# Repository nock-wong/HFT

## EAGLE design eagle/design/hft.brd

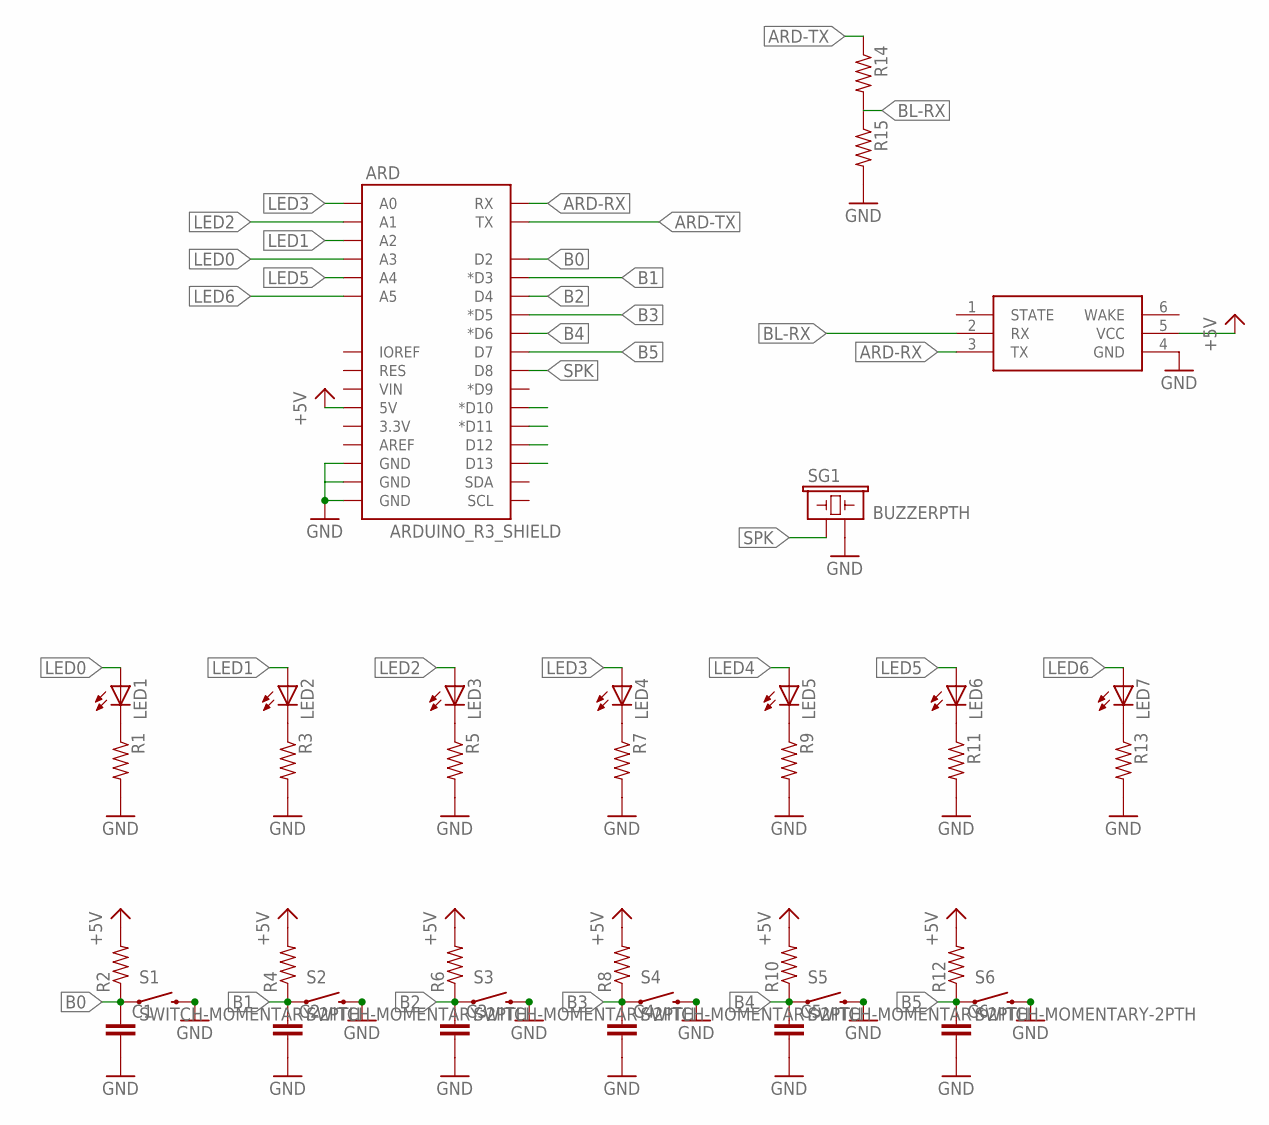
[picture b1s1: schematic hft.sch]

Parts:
ARD: ARDUINO_R3_SHIELD; UNO_R3_SHIELD
C1, C2, C3, C4, C5, C6: CAPACITOR0603-CAP; 0603-CAP
LED1, LED2, LED3, LED4, LED5, LED6, LED7: LED5MM
R1, R2, R3, R4, R5, R6, R7, R8, R9, R10, R11, R12, R13, R14, R15: RESISTOR; 0603-RES
S1, S2, S3, S4, S5, S6: SWITCH-MOMENTARY-2PTH; TACTILE-PTH
SG1: BUZZERPTH; BUZZER-12MM
U$8: HC-06; HC-06_BREAKOUT

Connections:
+5V: ARD.5V, R2.2, R4.2, R6.2, R8.2, R10.2, R12.2, U$8.5 (VCC)
ARD-RX: ARD.RX, U$8.3 (TX)
ARD-TX: ARD.TX, R14.1
B0: ARD.D2, C1.1, R2.1, S1.1
B1: ARD.D3 (*D3), C2.1, R4.1, S2.1
B2: ARD.D4, C3.1, R6.1, S3.1
B3: ARD.D5 (*D5), C4.1, R8.1, S4.1
B4: ARD.D6 (*D6), C5.1, R10.1, S5.1
B5: ARD.D7, C6.1, R12.1, S6.1
BL-RX: R14.2, R15.1, U$8.2 (RX)
GND: ARD.GND@0 (GND), ARD.GND@1 (GND), ARD.GND@2 (GND), C1.2, C2.2, C3.2, C4.2, C5.2, C6.2, R1.2, R3.2, R5.2, R7.2, R9.2, R11.2, R13.2, R15.2, S1.3 (2), S2.3 (2), S3.3 (2), S4.3 (2), S5.3 (2), S6.3 (2), SG1.- (2), U$8.4 (GND)
LED0: ARD.A3, LED1.A
LED1: ARD.A2, LED2.A
LED2: ARD.A1, LED3.A
LED3: ARD.A0, LED4.A
LED4: LED5.A
LED5: ARD.A4, LED6.A
LED6: ARD.A5, LED7.A
unnamed: LED1.K (C), R1.1
unnamed: LED2.K (C), R3.1
unnamed: LED3.K (C), R5.1
unnamed: LED4.K (C), R7.1
unnamed: LED5.K (C), R9.1
unnamed: LED6.K (C), R11.1
unnamed: LED7.K (C), R13.1
SPK: ARD.D8, SG1.+ (1)

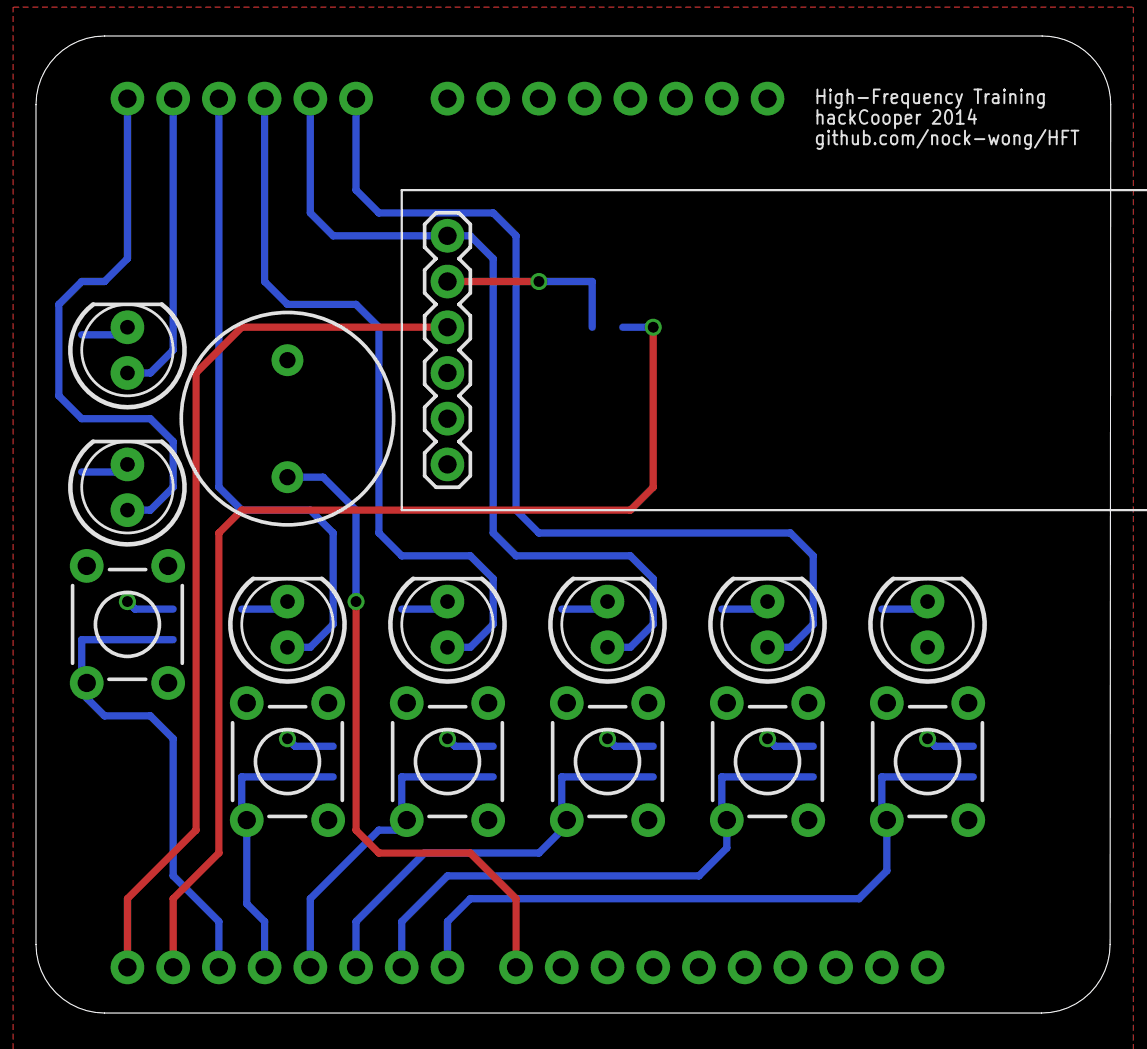
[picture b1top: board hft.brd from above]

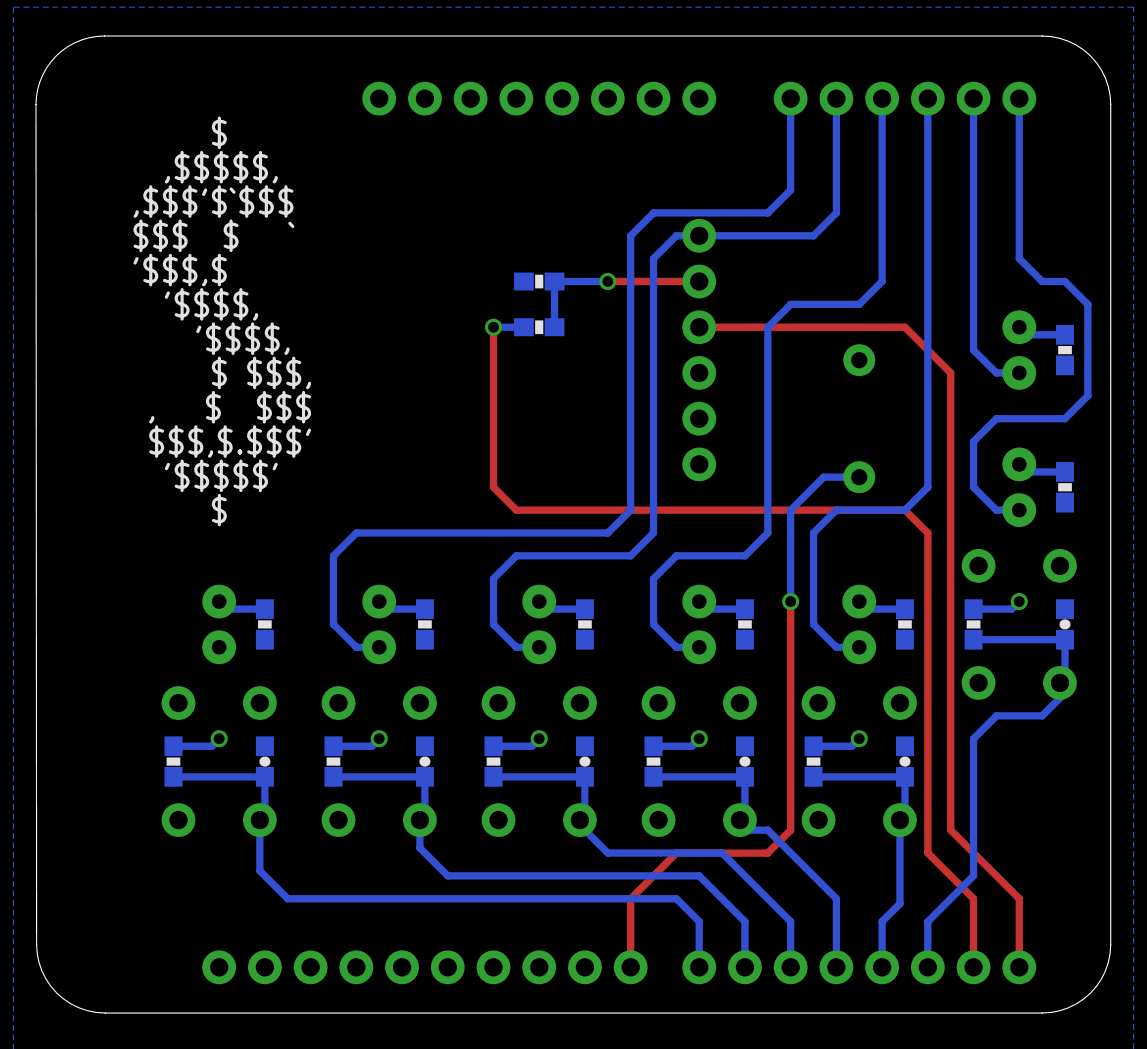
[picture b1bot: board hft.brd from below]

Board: 2 copper layers, 59.7 x 54.3 mm, 37 parts (21 on the bottom side), 25 nets.

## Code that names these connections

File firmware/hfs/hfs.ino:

#define COMMAND_BUTTON_STATES 'A'
#define COMMAND_GAME_LIGHTS 'B'
#define COMMAND_WON_OR_LOSE 'C'
#define COMMAND_END_CHAR 'X'
#define COMMAND_CONNECT 'F'
#define COMMAND_START 'D'
#define COMMAND_READY 'E'
#define COMMAND_GAME_END 'G'

#define LED0 8
#define LED1 9
#define LED2 10
#define LED3 11
#define LED4 12
#define LEDLOSE 2
#define LEDWIN 3
#define BUZZER 13
#define BUTTON0 A4
#define BUTTON1 A3
#define BUTTON2 A2
#define BUTTON3 A1
#define BUTTON4 A0

#define NOT_READY 0
#define READY 1

#define LOSE 0
#define WIN 1
#define NEUTRAL 2

#define BAUD 9600
#define LED_COUNT 5
#define BUTTON_COUNT 5
#define COMMAND_SIZE 20

const int g_leds_pins[LED_COUNT] = {LED0, LED1,LED2, LED3, LED4};
const int g_buttons_pins[BUTTON_COUNT] = {BUTTON0, BUTTON1, BUTTON2, BUTTON3, BUTTON4};

int g_command_ready = false;
int g_command_index = 0;
int g_command_in[COMMAND_SIZE];

int g_buttons_changed = false;
int g_leds_states[] = {0, 0, 0, 0, 0};
int g_buttons[] = {0, 0, 0, 0, 0};

int g_connected = false;
int g_start = false;
int g_end = false;

int g_won = NEUTRAL;

void 
setup (void) 
{
  pinMode(LED0, OUTPUT);
  pinMode(LED1, OUTPUT);
  pinMode(LED2, OUTPUT);
  pinMode(LED3, OUTPUT);
  pinMode(LED4, OUTPUT);
  pinMode(LEDWIN, OUTPUT);
  pinMode(LEDLOSE, OUTPUT);
  
  pinMode(BUTTON0, INPUT);
  pinMode(BUTTON1, INPUT);
  pinMode(BUTTON2, INPUT);
  pinMode(BUTTON3, INPUT);
  pinMode(BUTTON4, INPUT);

  pinMode(BUZZER, OUTPUT);
  Serial.begin(BAUD);
}

void
loop (void)
{ 
  // Wait for connection to game
  while(g_connected == false)
  {
    send_connect();
    read_command();
    delay(500);
  }
  // Wait for game to start
  while(g_start == false)
  {
    read_command();
  }
  // Game start
  while(g_start == true && g_end == false)
  {
    g_won = NEUTRAL;
    read_command();
    update_display();
    read_buttons();
    if (g_buttons_changed == true)
    {
      send_buttons_states();
    }
  }
  // Game end
  g_connected = false;
  g_start = false;
  g_end = false;
}

void send_connect()
{
  Serial.print(COMMAND_CONNECT);
  Serial.print(COMMAND_END_CHAR);
}

void read_command() 
{
  while (Serial.available())
  {
    int r = Serial.read();
    g_command_in[g_command_index] = r;
    g_command_index++;
    if (r == COMMAND_END_CHAR)
    {
      process_command();
    }
  }
  return;
}

void process_command()
{
  // Confirm connect
  if (g_command_in[0] == COMMAND_CONNECT)
  {
    g_connected = true;
  }
  // Start game
  if (g_command_in[0] == COMMAND_START)
  {
    g_start = true;
    start_sequence();
    send_ready();
  }
  // Sets the game lights
  if (g_command_in[0] == COMMAND_GAME_LIGHTS)
  {
    for (int i = 0; i < LED_COUNT; i++)
    {
      int state = LOW;
      switch(g_command_in[i+1])
      {
        case '0':
          state = LOW;
          break;
        case '1':
          state = HIGH;
          break;
        default:
          state = LOW;
          break;
      }
      g_leds_states[i] = state;
    }
  }
  // Sets the WIN/LOSE lights
  else if (g_command_in[0] == COMMAND_WON_OR_LOSE)
  {
    int state = LOSE;
    if (g_command_in[1] == '0')
    {
      state = LOSE;
    }
    else if (g_command_in[1] == '1')
    {
      state = WIN;
    }
    else if (g_command_in[1] == '2')
    {
      state = NEUTRAL;
    }
    g_won = state;
   }
  // Sets the end game
  else if (g_command_in[0] == COMMAND_GAME_END)
  {
    g_end = true;
    if (g_command_in[1] == '1')
    {
      digitalWrite(LEDLOSE, LOW);      
      digitalWrite(LEDWIN, HIGH);
      win();
    }
    else if (g_command_in[1] == '0')
    {
      digitalWrite(LEDLOSE, HIGH);      
      digitalWrite(LEDWIN, LOW);
      lose();
    } 
  }
  clear_command_in();
}

void start_sequence()
{
  /*
  for(int i = 0; i < LED_COUNT; i++)
  {
    digitalWrite(g_leds_pins[i], HIGH);
  }
  */
  digitalWrite(LEDLOSE, HIGH);
  playMelody("c", 1000);
  digitalWrite(LEDLOSE, LOW);
  delay(100);
  
  digitalWrite(LEDLOSE, HIGH);
  playMelody("c", 1000);
  digitalWrite(LEDLOSE, LOW);
  delay(100);
  
  digitalWrite(LEDLOSE, HIGH);
  playMelody("c", 1000);
  digitalWrite(LEDLOSE, LOW);
  delay(100);

  digitalWrite(LEDWIN, HIGH);
  playMelody("z", 1000);  
  /*
  for (int j = 0; j < 3; j++)
  {
    for(int i = 0; i < LED_COUNT; i++)
    {
      digitalWrite(g_leds_pins[i], HIGH);
    }
    delay(500);
    for(int i = 0; i < LED_COUNT; i++)
    {
      digitalWrite(g_leds_pins[i], LOW);
    }
    delay(500);
  }
  */
  return;
}

void send_ready()
{
  Serial.print(COMMAND_READY);
  Serial.print(COMMAND_END_CHAR);
  return;
}

void update_display() 
{
  for (int i = 0; i < 5; i++)
  {
    digitalWrite(g_leds_pins[i], g_leds_states[i]);
  }
  switch (g_won)
  {
    case WIN:
      digitalWrite(LEDWIN, HIGH);
      digitalWrite(LEDLOSE, LOW);
      correct();
      break;
    case LOSE:
      digitalWrite(LEDWIN, LOW);
      digitalWrite(LEDLOSE, HIGH);
      incorrect();
      break;
    case NEUTRAL:
      digitalWrite(LEDWIN, LOW);
      digitalWrite(LEDLOSE, LOW);
      break;
  }
  return;
}

void clear_command_in ()
{
  for (int i = 0; i < COMMAND_SIZE; i++)
  {
    g_command_in[i] = 0;
  }
  g_command_index = 0;
  g_command_ready = false;
  return;
}

void send_buttons_states()
{
  Serial.print(COMMAND_BUTTON_STATES);
  for (int i = 0; i < BUTTON_COUNT; i++)
  {
    Serial.print(g_buttons[i]);
  }
  Serial.print(COMMAND_END_CHAR);
}

void read_buttons (void)
{
  g_buttons_changed = false;
  int buttons_readings[BUTTON_COUNT];
  // Read buttons
  for (int i = 0; i < BUTTON_COUNT; i++)
  {
    buttons_readings[i] = !digitalRead(g_buttons_pins[i]);
  }
  // Compare current to previous
  boolean buttons_different = false;
  for (int i = 0; i < BUTTON_COUNT; i++) 
  {
    if (g_buttons[i] != buttons_readings[i])
    {
      g_buttons[i] = buttons_readings[i];
      buttons_different = true;
    }
  }
  // Check that buttons aren't all 0
  boolean buttons_all_zero = true;
  for (int i = 0; i < BUTTON_COUNT; i++) 
  {
    if (g_buttons[i] != 0)
    {
      buttons_all_zero = false;
    }
  }
  g_buttons_changed = buttons_different && !buttons_all_zero;
}


/* Sound */
int length(char *n)
{
  int i;
  for(i = 0; n[i] != '\0'; i++);
  return i;
}

void playNote(char c)
{
  tone(BUZZER, note(c), 500);
}

void playMelody(char *melody, int nduration)
{
  int l = length(melody);
  for(int n = 0; n < l; n++) {
    playNote(melody[n]);
    delay(nduration);
  }
}

void playProgression(char *prog, int nduration)
{
  int l = length(prog);
  for(int t = 0; t < l; t++)
    playMelody(triad(prog[t]), nduration);
}

int note(char c)
{
  switch(c) {
    case 'c' : return 262;
    case 'C' : return 277;
    case 'd' : return 294;
    case 'D' : return 311;
    case 'e' : return 330;
    case 'f' : return 349;
    case 'F' : return 370;
    case 'g' : return 392;
    case 'G' : return 415;
    case 'a' : return 440;
    case 'A' : return 466;
    case 'b' : return 494;
    case 'z' : return 524;
  }
}

char *triad(char c)
{
  switch(c) {
     case 'c' : return "cDg";
     case 'C' : return "ceg";
     case 'd' : return "dfa";
     case 'D' : return "dFa";
     case 'e' : return "egb";
     case 'E' : return "eGb";
     case 'f' : return "fGz";
     case 'F' : return "faz";
     case 'G' : return "dgb";
     case 'a' : return "cea";
     case 'A' : return "Cea";
     case 'b' : return "dFb";
     case 'B' : return "DFb";
     case 'z' : return "zgDc";
     case 'Z' : return "zgec";
     default  : return "ccc";
  }
}

void correct()
{
  playMelody("cegz", 20);
}

void incorrect()
{
  playMelody("cDFA", 20);
}

void win()
{
  playProgression("CFdGZ", 100);
}

void lose()
{
  playMelody("zbAaG", 300);
}

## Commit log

2014-02-13 First commit.
    Add Eagle design files.
2014-02-13 Re-organize directory and update .gitignore.
2014-02-13 Add firmware and game controller code.
